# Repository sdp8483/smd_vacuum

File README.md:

# Manual Pick and Place SMD Vacuum

*Copy from blog post: https://samueldperry.com/2021/06/07/manual-pick-and-place-smd-vacuum/*

Until recently I used tweezers when populating surface mount parts on a PCB. Browsing around on YouTube late one night I stumbled upon a video by [SDG Electronics](https://www.youtube.com/channel/UCMiC9bSMux7i2Ds6sIqDaFg) about making a [Manual Pick and Place SMD Vacuum](https://www.youtube.com/watch?v=9G510G2gmdo&t=24s). There is also a [part 2](https://www.youtube.com/watch?v=1FnGqH_WkL4&list=RDCMUCMiC9bSMux7i2Ds6sIqDaFg&index=3) for those interested. I was then motivated to make up my own since it looked so much easier then using tweezers. There was no parts list from SDG Electronics that I could find so I set about searching for suitable components and designing my own simple controller PCB. Below is a description of the mechanical and electrical designing of the SMD Vacuum that I ended up building.

## Bill Of Materials

Below is a bill of materials with supplier links of all the major mechanical and electrical components. The PCB controller components are presented in a separate BOM below without suggested supplier links since all the components are generic and can be sourced from the usual suspects.
No. |Item|	Qty.|	Suggested Supplier Link
-----|----|-----|--------------------------|
1|	Metal Enclosure, 7.5″ x 9.8″ x 3.2″|	1|	[Jameco](https://www.jameco.com/webapp/wcs/stores/servlet/ProductDisplay?langId=-1&storeId=10001&catalogId=10001&productId=209358)
2|	LED Panel Mounting Hardware|	10|	[Jameco](https://www.jameco.com/webapp/wcs/stores/servlet/ProductDisplay?langId=-1&storeId=10001&catalogId=10001&productId=23077)
3|	12V Diaphragm Vacuum Pump|	1|	[eBay](https://www.ebay.com/itm/221615572829?epid=1545518177&hash=item339951475d:g:GFgAAOSwhMFZqyRF)**
4|	12V Pneumatic Shutoff Valve|	1|	[eBay](https://www.ebay.com/itm/114832826636?hash=item1abc91e10c:g:bG0AAOSwbg9gtVNb)
5|	1/4″ NPT Inline Filter/Snubber|	1|	[eBay](https://www.ebay.com/itm/132229655610)
6|	Vacuum Pick & Place Tool|	1|	[DigiKey](https://www.digikey.com/en/products/detail/apex-tool-group/T0052918499N/1801476?s=N4IgTCBcDaICoAYEFYwE4CMAOALGtAciALoC%2BQA)
7|	1/4″ PVC Tubing|	50ft|	[McMaster-Carr](https://www.mcmaster.com/5233K52/)
8|	1/4″ Tube Fitting, Through Wall|	1|	[McMaster-Carr](https://www.mcmaster.com/5779K272/)
9|	1/4″ Tube Fitting to 1/4″ NPT Male|	3|	[McMaster-Carr](https://www.mcmaster.com/7880T125/)
10|	12V 1.3A AC to DC Power Supply|	1|	[Jameco](https://www.jameco.com/webapp/wcs/stores/servlet/ProductDisplay?langId=-1&storeId=10001&catalogId=10001&productId=1919051)
11|	1/4″ Phone Jack|	2|	[Jameco](https://www.jameco.com/webapp/wcs/stores/servlet/ProductDisplay?langId=-1&storeId=10001&catalogId=10001&productId=297537)
12|	IEC 320-C14 Power Entry Module with Fuse|	1|	[Amazon](https://www.amazon.com/Module-Socket-Connector-Blades-Holder/dp/B07TQMW2D9/ref=sr_1_1?crid=3QOD60WNOGIO3&dchild=1&keywords=power+entry+module+with+fuse&qid=1622939893&sprefix=power+entry+mo%2Caps%2C180&sr=8-1)*
13|	Rocker Switch|	1|	[Amazon](https://www.amazon.com/QTEATAK-Rocker-Switch-Position-Terminals/dp/B08B84H8WL/ref=sr_1_5?crid=1LWHY6BQHJB3N&dchild=1&keywords=rocker+switch&qid=1622940058&sprefix=rocker+%2Caps%2C186&sr=8-5)*
14|	3mm LED, Red/Green|	3|	[Amazon](https://www.amazon.com/Chanzon-100pcs-colors-Emitting-Assorted/dp/B01AUI4W5U/ref=sr_1_3?dchild=1&keywords=3mm+led&qid=1622940238&sr=8-3)*
15|	100k Potentiometer with Knob|	1|	[Amazon](https://www.amazon.com/TWTADE-rv24yn20s-Variable-Potentiometer-Regulation/dp/B07DHFYLRV/ref=sr_1_6?crid=1AW49CSX56C4B&dchild=1&keywords=100k+potentiometer&qid=1622940371&sprefix=100k+po%2Caps%2C186&sr=8-6)*
16|	Foot Switch with 1/4″ Plug|	1|	[eBay](https://www.ebay.com/itm/272420357567)
17|	Various Fasteners and Similar Hardware|		
18|	Assembled Controller|	1|	See BOM Below

*I didn’t buy these exact items since I had them already from previous projects but these should be equivalent to what I used. Substitutions are possible for items you have on hand.

**When I was looking for a small vacuum pump eBay was flooded with the Parker 12V Dual Head Vacuum Pump which is what I got. But now it seems to be out of stock and since it looks like it was a surplus item it is probably out of stock for good. The linked vacuum pump looks like it will work just as well but I have not tested it.

No.|	Item|	Qty.
---|--------|-------
1|	PCB|	1
2|	10nF Ceramic Capacitor|	1
3|	100uF 25V Electrolytic Capacitor|	2
4|	1N4148 Diode|	2
5|	1N4007 Diode|	2
6|	IRF5305 P-channel MOSFET|	1
7|	N-channel MOSFET|	2
8|	4.7k 1/4W Through Hole Resistor|	1
9|	1k 1/4W Through Hole Resistor|	7
10|	NE555P 555 Timer|	1
11|	817 Optocoupler|	1
12|	8 pin DIP IC Socket|	1
13|	2 Position Screw Terminal|	5
14|	JST Socket with Matching Connectors and Pins|	2

## Controller PCB

Yes this project uses a 555 timer, as a electronics hobbyist I am contractually obligated to use it in at least one project. While the solution by SDG Electronics with a microcontroller is perfectly valid and what I would have normally used, I decided to finally use a 555 timer in a project. I hate the 555 timer and find it completely unnecessary in today’s microcontroller dominated world. Why use a IC that requires external components when a few lines of code and less components will produce the same result with more accurate timings? I have to admit that at the end of this project I had a little respect for the 555 timer and found it a good challenge to try to manipulate it to do what I wanted. I may briefly consider it in future simple projects.

The PCB is designed to enable milling on a CNC router such as the 3018 Pro and that is what I did. [Gerbers](https://github.com/sdp8483/smd_vacuum/tree/main/pcb/gerber) are available but be warned I did not pay any attention to the silkscreen so some component labels could be in strange spots or missing. If you want to get your PCBs made I would suggest opening the KiCAD design files and fixing the silkscreen labels before.

The circuit is fairly simple, closing SW1 (the foot switch) turns on the vacuum pump and opens the shutoff valve. LED D2 and D3 will be illuminated. Releasing SW1 will close the shutoff valve turning off suction upstream of the shutoff valve and LED D3 will turn off. The vacuum pump will continue to run based on the position of the 100k potentiometer, somewhere between 1 and 15 seconds.

PCB assembly is easy when following the [interactive bom](https://github.com/sdp8483/smd_vacuum/tree/main/pcb/bom). In the pictures you may notice mine has a bodge since my first design neglected the reset on power circuitry and I had to add that after I noticed that sometimes on first power up the controller would turn on the vacuum pump. The PCB design has been updated with those components so no need for you to bodge them in.

## Assembly

I will go over briefly how I assembled my SMD Vacuum but will omit many details since you most likely will not be using the same vacuum pump and you may wish your layout to be slightly different.

First thing I did was to arrange all the components inside the enclosure so that I could see if everything would fit. I roughly knew that I wanted to keep the power supply and its AC wiring on the left of the case, with the controller in the middle and the pneumatics on the right side of the case. I also arranged the front and back panels to look like I wanted. Pencil works great since it can easily be cleaned off later.

I started with mounting the AC power input socket, rocker switch, and 12V power supply. I wired the rocker switch to cut power to the input of the 12V power supply so that when the unit is turned off there will be zero current draw. Don’t forget to attach the earth ground from the AC socket to the case using a bolt and star washer. Sand off some of the paint under the washer on the case to make a good metal to metal connection. Also attach the earth ground of the 12V power supply to this same point. This way the case is grounded and is safer.

I then mounted the controller PCB using nylon standoffs near the center of the case and oriented it so that the power input terminal is close to the 12V power supply. At the same time I mounted the 100k potentiometer, LEDs, and 1/4″ jacks. I used two 1/4″ jacks in parallel because I wanted both the front and back panels to have a jack. This way I can plug the foot switch into whatever panel is most convenient for wire management.

For the pnumatics I 3D printed some standoffs so that they would not be resting directly on the case. This was mostly done because of the length of fasteners I had and also to dampen the noise produced by the vacuum pump. I plumbed the punmatics as shown below with the shutoff valve between the pump and the filter followed by the panel mounted 1/4″ tube fitting. The filter is absolutely necessary as I have already sucked up quite a few 0603 parts and having the filter saves the shutoff valve and pump from damage.

That was about all the steps I took for assembly, fairly simple. The aluminum bars in the pictures were added to increase the stiffness of the front and back panel when plugging in connectors and tubing.

## Hand piece

Aside from the vacuum pump the second most important item for this build is the hand piece. This is the part that you hold and use to pickup SMD parts. I was able to find a used Weller WVP on eBay. I would suggest looking there or other used market places first since it is relatively expensive brand new for some reason. The part number to search for is T0052918499N or look for replacement parts for a Weller WR3M Station. [DigiKey](https://github.com/sdp8483/smd_vacuum/tree/main/pcb/bom) sells a new Weller WVP for $88. The Weller WVP is adapted to the SMD Vacuum by cutting a small section of the 1/4″ PVC tubing and inserting the plastic nozzle on the end hand piece into the tubing as shown below. Finally block the hole on the side of the Weller WVP since we are using to foot pedal to control suction and not your finger.

This hand piece feels really nice and works well for me. Having said that if you cannot find one for a decent price or feel like making your own hand piece I did do a little experimentation and found that it is possible to make something similar while not as well polished. I used a [1/8″ OD Brass Tube](https://www.mcmaster.com/8859K19/) and connected it to the front port of the SMD Vacuum using [1/4″ OD Soft Tygon PVC Tubing](https://www.mcmaster.com/5552k23/). The clear PVC tubing used inside the SMD Vacuum is a little stiff for my liking and I found that Tygon tubing is slightly more pliant. The photos below show the rough setup I was experimenting with before I found the Weller Hand Piece. My plan was to 3D print a case to go around the brass tube for gripping and to also 3D print adapters so that the nozzles could connect better to the brass tube. As pictured it works fine although not very ergonomic. For nozzles I used a rubber protective cover that comes on the engraving bits for the 3018 pro with a small hole that I drilled in the end. This setup was a rough prototype that I would have refined more had I not picked up a Weller WVP.

## Nozzles

Nozzles, you will need some. The Weller WVP comes with some nozzles and suction cup tips. You can also get these nozzle and cups with one of the cheap [vacuum suction pens](https://www.amazon.com/Jiayouy-Precision-Component-Placement-Interchangeable/dp/B08SWG12G3/ref=sr_1_3?dchild=1&keywords=smd+pen&qid=1623079740&sr=8-3). These nozzles and suction cups are great for picking up larger SMD packages like microcontrollers and power MOSFETs but they are not useful for small packages such as 0603 resistors and capacitors. The suction cup gets in the way and grips the part so well that it will not release when suction is turned off. Removing the suction cup is not possible since the nozzle ID is large enough that a 0603 resistor can get sucked up it. Remember that filter, this is why it is installed before the shutoff valve.

What I found that works great for these small packages is [blunt tip needles for syringes](https://www.amazon.com/dp/B07RSTQ6RV?psc=1&ref=ppx_yo2_dt_b_product_details). I got a variety pack with 14ga, 16ga,18ga, 20ga, 22ga and 25ga needles along with some syringes. I found the 20ga needle (pink) to be the perfect size for picking up 0603 packages along with SOT-23 transistors and some larger packages. The part drops off as soon a suction is off and you can see the part while manipulating it. The only problem is that the nozzle requires you to work with the hand piece vertical since it does not have the angle on it like the nozzles that came with the Weller WVP. If I get adventurous I may try bending one someday but for now I found working vertical gave me better position control.

## Conclusion

That wraps up this project. I am very happy with how it turned out and its function. I successfully assembled a small run of 10 PCBs with 64 components per board using this SMD Vacuum without any issues. Utilizing the blunt needle tip along with one of the suction cup tips that came with the Weller WVP I was able to handle all the SMD parts for those PCBs. The smallest package size was 0603 and the largest package was a ESP-12F WiFi module. The SMD Vacuum had enough suction power to lift everything and made placement easy. Goodby tweezers, hello SMD Vacuum.

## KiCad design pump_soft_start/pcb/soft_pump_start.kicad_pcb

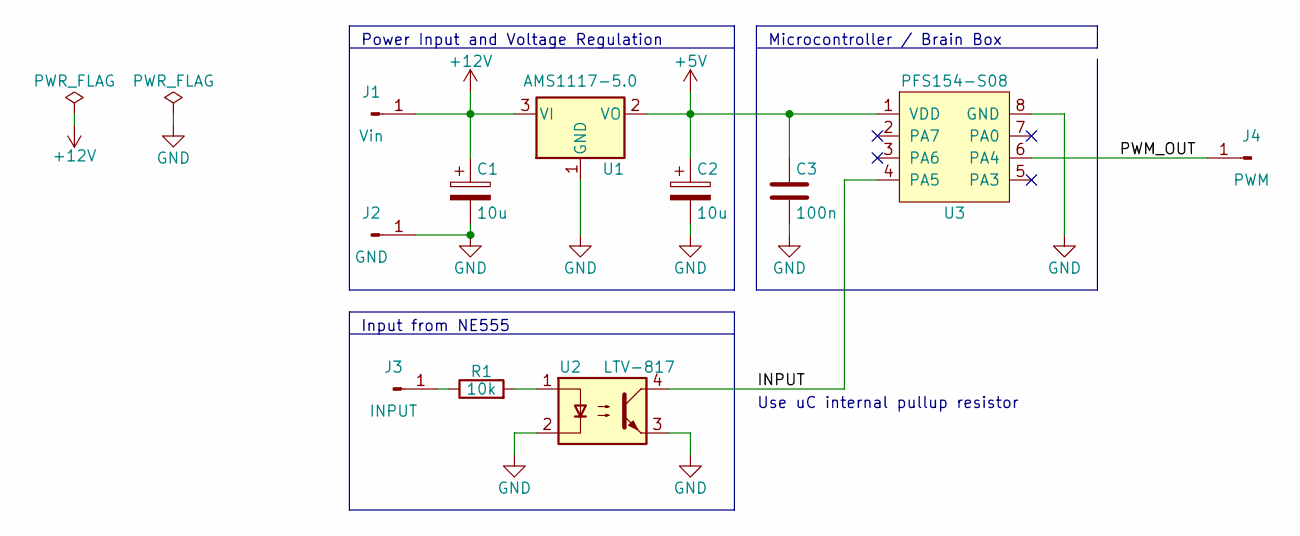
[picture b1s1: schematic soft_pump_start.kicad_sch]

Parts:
C1, C2: 10u; CP_Radial_D5.0mm_P2.50mm
C3: 100n; C_0603_1608Metric_Pad1.08x0.95mm_HandSolder
J1: Vin; SolderWire-0.5sqmm_1x01_D0.9mm_OD2.1mm
J2: GND; SolderWire-0.5sqmm_1x01_D0.9mm_OD2.1mm
J3: INPUT; SolderWire-0.5sqmm_1x01_D0.9mm_OD2.1mm
J4: PWM; SolderWire-0.5sqmm_1x01_D0.9mm_OD2.1mm
R1: 10k; R_0603_1608Metric_Pad0.98x0.95mm_HandSolder
U1: AMS1117-5.0; SOT-223-3_TabPin2
U2: LTV-817; DIP-4_W7.62mm
U3: PFS154-S08; SOP-8_3.9x4.9mm_P1.27mm

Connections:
+5V: C2.1, C3.1, U1.2 (VO), U3.1 (VDD)
+12V: C1.1, J1.1, U1.3 (VI)
/INPUT: U2.4, U3.4 (PA5)
/PWM_OUT: J4.1, U3.6 (PA4)
GND: C1.2, C2.2, C3.2, J2.1, U1.1 (GND), U2.2, U2.3, U3.8 (GND)
unnamed: J3.1, R1.1
unnamed: R1.2, U2.1

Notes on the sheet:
Microcontroller / Brain Box
Input from NE555
Use uC internal pullup resistor
Power Input and Voltage Regulation

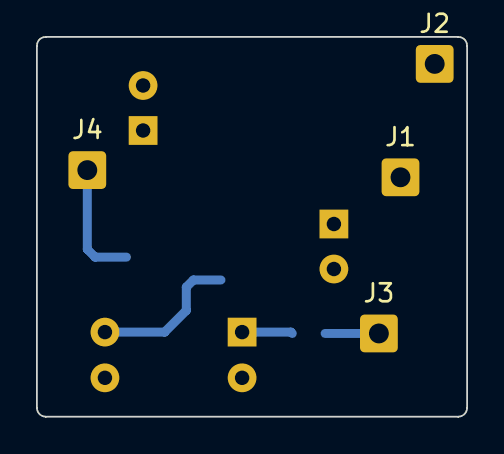
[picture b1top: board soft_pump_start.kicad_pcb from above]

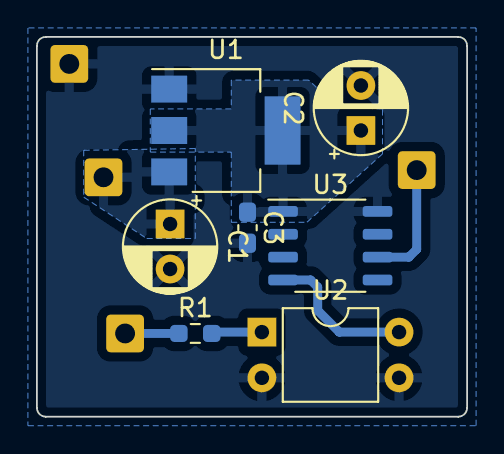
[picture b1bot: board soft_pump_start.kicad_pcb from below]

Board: 2 copper layers, 23.9 x 21.1 mm, 11 parts (7 on the bottom side), 7 nets.

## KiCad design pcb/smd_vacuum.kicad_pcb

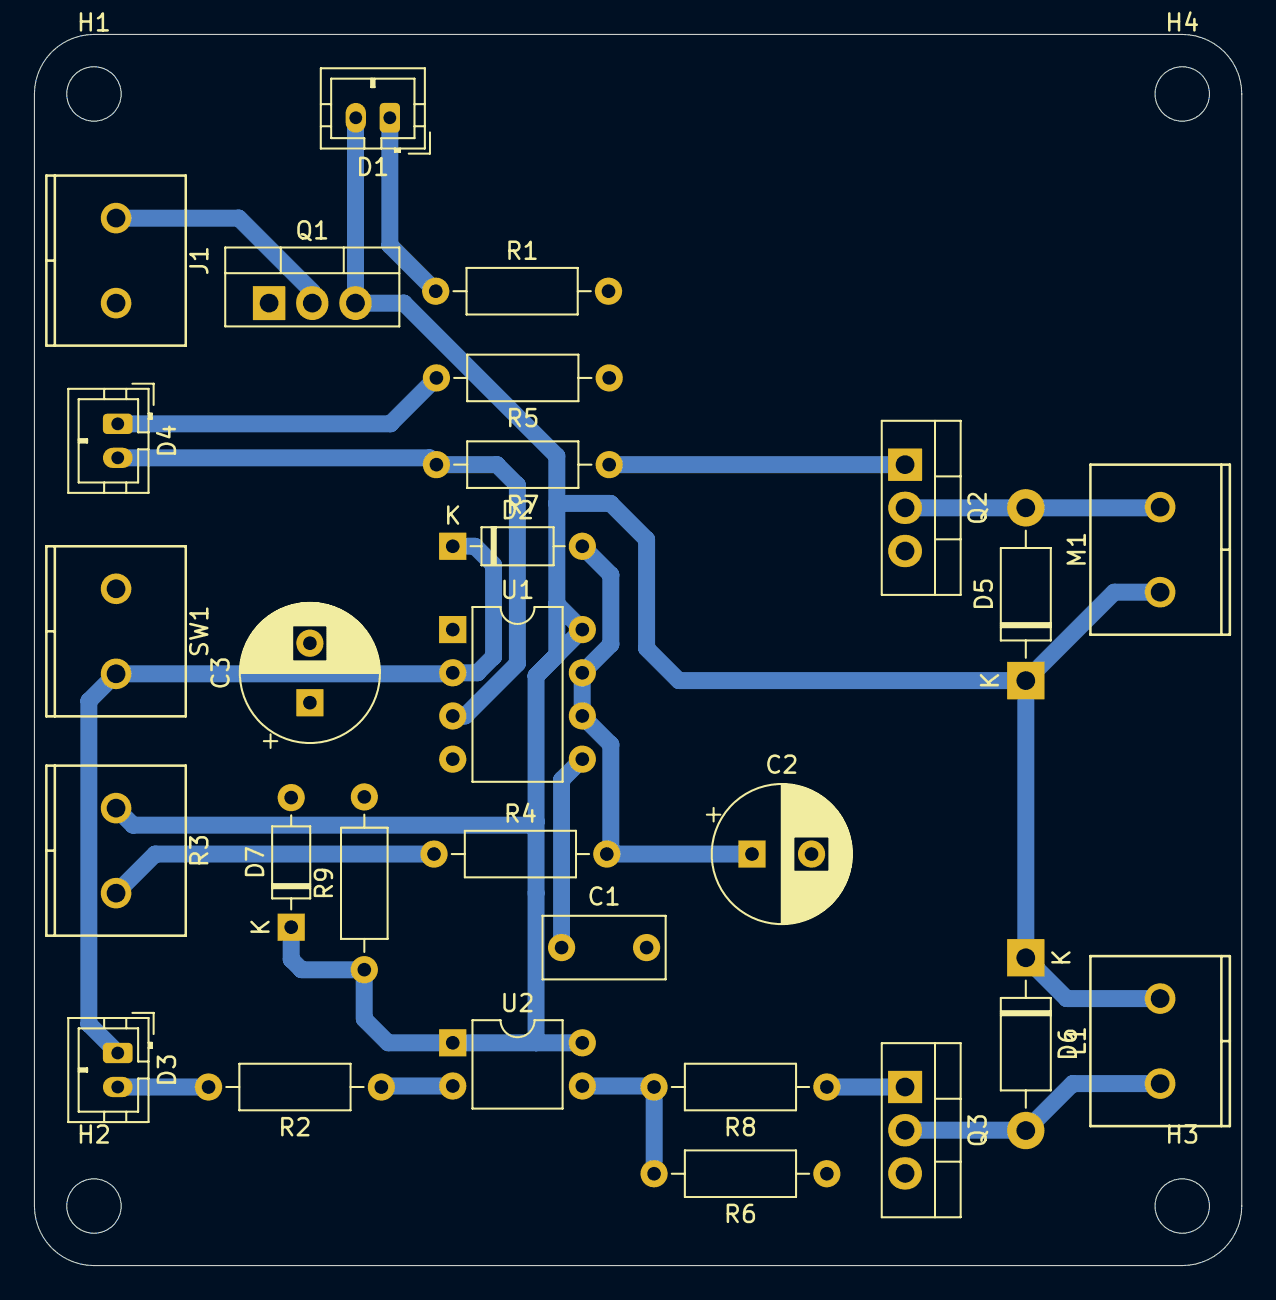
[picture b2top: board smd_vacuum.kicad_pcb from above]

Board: 2 copper layers, 71.0 x 72.4 mm, 32 parts (0 on the bottom side), 18 nets.

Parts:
C1: 10n; C_Rect_L7.0mm_W3.5mm_P5.00mm
C2, C3: 100u; CP_Radial_D8.0mm_P3.50mm
D1, D3, D4: LED; JST_PH_B2B-PH-K_1x02_P2.00mm_Vertical
D2, D7: 1N4148; D_DO-35_SOD27_P7.62mm_Horizontal
D5, D6: 1N4007; D_DO-41_SOD81_P10.16mm_Horizontal
H1, H2, H3, H4: MountingHole; MountingHole_3.2mm_M3
J1: PWR; WJ127-5.0-2P
L1: L; WJ127-5.0-2P
M1: Motor_DC; WJ127-5.0-2P
Q1: IRF5305; TO-220-3_Vertical
Q2, Q3: Q_NMOS_GDS; TO-220-3_Vertical
R1, R2, R5, R6, R7, R8, R9: 1k; R_Axial_DIN0207_L6.3mm_D2.5mm_P10.16mm_Horizontal
R3: 100k; WJ127-5.0-2P
R4: 4k7; R_Axial_DIN0207_L6.3mm_D2.5mm_P10.16mm_Horizontal
SW1: SW_SPST; WJ127-5.0-2P
U1: NE555P; DIP-8_W7.62mm
U2: EL817; DIP-4_W7.62mm

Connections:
+12V: D1.2, D5.1, D6.1, D7.1, L1.2, M1.1, Q1.3, R3.1, R9.1, U1.8, U2.1, U2.4
GND: C1.2, C2.2, C3.2, J1.2, Q1.1, Q2.3, Q3.3, R1.2, R5.1, R6.1, SW1.1, U1.1
unnamed: C1.1, U1.5
unnamed: C2.1, D2.2, R4.2, U1.6, U1.7
unnamed: C3.1, D7.2, R9.2, U1.4
unnamed: D1.1, R1.1
unnamed: D2.1, D3.1, SW1.2, U1.2
unnamed: D3.2, R2.2
unnamed: D4.1, R5.2
unnamed: D4.2, R7.2, U1.3
unnamed: D5.2, M1.2, Q2.2
unnamed: D6.2, L1.1, Q3.2
unnamed: J1.1, Q1.2
unnamed: Q2.1, R7.1
unnamed: Q3.1, R8.1
unnamed: R2.1, U2.2
unnamed: R3.2, R4.1
unnamed: R6.2, R8.2, U2.3

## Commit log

2021-04-25 init commit
2021-04-25 add terminal 3d models
2021-04-25 board layout
2021-04-25 plot gerbers
2021-04-25 generate gcode
2021-04-25 create 2nd cuRemoval
2021-04-25 update spindle speed
2021-04-27 add polarity protection pmos part number
2021-04-27 add rc to 555 reset for power on reset
2021-04-27 layout pcb with reset circuitry
2021-05-16 add spacers
2021-06-06 output schematic
2021-06-06 create iBOM
2021-06-07 update with info and pictures
2022-05-03 ignore kicad backups
2022-05-03 to new kicad version
2022-05-03 export updated pcb gerbers
2022-05-03 move origin
2022-05-03 updated gcode
2022-06-27 create file
2023-01-21 create soft start circuit
2023-01-21 init fw code
2023-01-22 PWM timing fixes for acceptable startup lag
2023-02-01 fw build
